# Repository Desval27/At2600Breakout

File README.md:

# Breadboard Friendly Breakout Board for Atari&trade; 2600 Cartridges

## Ready to Order Gerber Files
- [Default](hardware/gerber_to_order/At2600Breakout_22.86x35.56mm_for_Default.zip)
- [Elecrow](hardware/gerber_to_order/At2600Breakout_22.86x35.56mm_for_Elecrow.zip)
- [FusionPCB](hardware/gerber_to_order/At2600Breakout_22.86x35.56mm_for_FusionPCB.zip)
- [JLCPCB](hardware/gerber_to_order/At2600Breakout_22.86x35.56mm_for_JLCPCB.zip)
- [PCBWay](hardware/gerber_to_order/At2600Breakout_22.86x35.56mm_for_PCBWay.zip)

## ⚠️ Disclaimer

This project is provided **"as is"**, without warranty of any kind, express or implied,
including but not limited to the warranties of merchantability, fitness for a
particular purpose, and noninfringement.

This is a DIY electronics project intended for educational and experimental use.
Use at your own risk.

The author assumes **no responsibility or liability** for any damage, injury, or loss
resulting from the use or misuse of this design, including but not limited to:

* Damage to connected equipment (Eurorack modules, power supplies, computers, etc.)
* Incorrect assembly or wiring
* Use with incompatible voltages or signal levels
* Personal injury

### Electrical Safety

This project may interface with:

* ±12V Eurorack power rails
* External control voltages (CV)
* Digital and analog circuitry

Improper handling may result in damage or unsafe conditions.

You are responsible for:

* Verifying all connections before powering the system
* Ensuring correct polarity of power connections
* Confirming voltage ranges and signal compatibility
* Using appropriate protection circuits where necessary

### No Guarantees

Schematics, PCB layouts, and code are provided for reference only.
They may contain errors, omissions, or design flaws.

**Always review and validate the design before building or using it.**

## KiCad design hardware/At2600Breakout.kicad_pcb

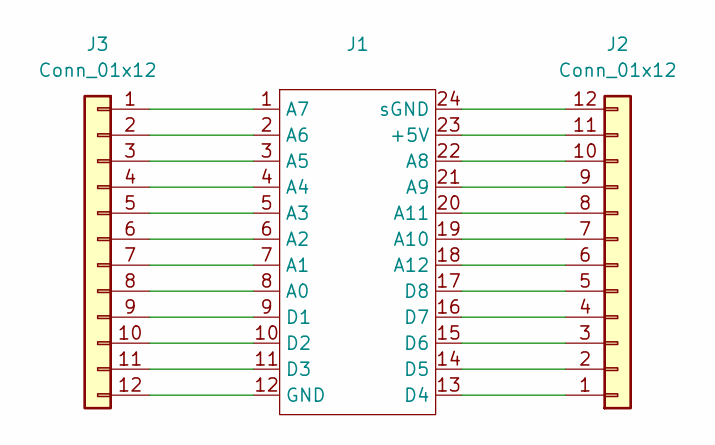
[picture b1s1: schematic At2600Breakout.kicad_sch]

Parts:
J1: 02x12 Cartridge Connector
J2, J3: Conn_01x12; PinHeader_1x12_P2.54mm_Vertical

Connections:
unnamed: J1.23 (+5V), J2.11
unnamed: J1.8 (A0), J3.8
unnamed: J1.7 (A1), J3.7
unnamed: J1.6 (A2), J3.6
unnamed: J1.5 (A3), J3.5
unnamed: J1.4 (A4), J3.4
unnamed: J1.3 (A5), J3.3
unnamed: J1.2 (A6), J3.2
unnamed: J1.1 (A7), J3.1
unnamed: J1.22 (A8), J2.10
unnamed: J1.21 (A9), J2.9
unnamed: J1.19 (A10), J2.7
unnamed: J1.20 (A11), J2.8
unnamed: J1.18 (A12), J2.6
unnamed: J1.9 (D1), J3.9
unnamed: J1.10 (D2), J3.10
unnamed: J1.11 (D3), J3.11
unnamed: J1.13 (D4), J2.1
unnamed: J1.14 (D5), J2.2
unnamed: J1.15 (D6), J2.3
unnamed: J1.16 (D7), J2.4
unnamed: J1.17 (D8), J2.5
unnamed: J1.12 (GND), J3.12
unnamed: J1.24 (sGND), J2.12

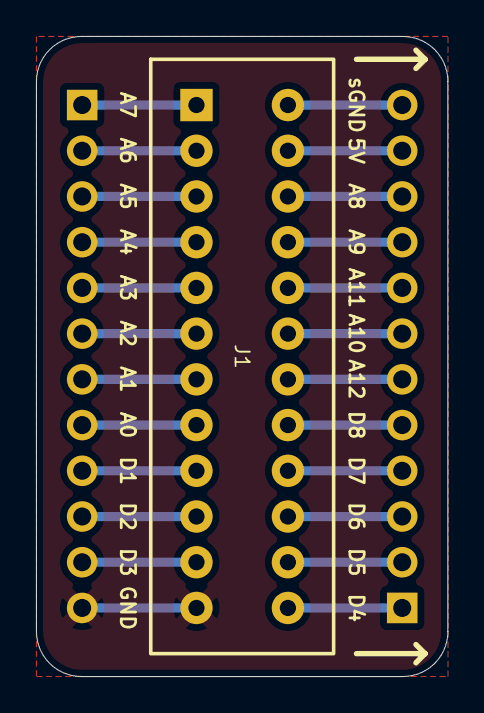
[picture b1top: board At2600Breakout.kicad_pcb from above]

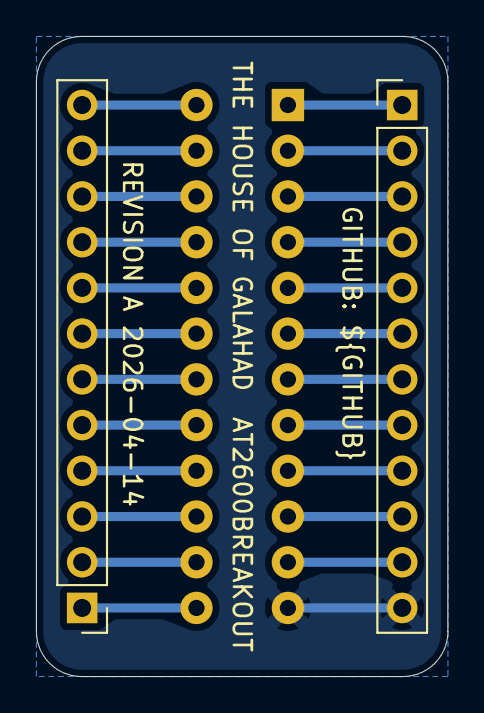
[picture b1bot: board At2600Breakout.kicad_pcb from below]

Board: 2 copper layers, 22.9 x 35.6 mm, 3 parts (2 on the bottom side), 24 nets.

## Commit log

2026-04-14 Add disclaimer and safety information to README
    Added project disclaimer and electrical safety guidelines.
2026-04-14 Add MIT License to the project
2026-04-19 Fix formatting and update title in README.md
2026-04-19 Added Gerber to Order Files
2026-04-19 Fix gitignore
2026-04-19 Fix git
2026-04-19 Add Gerber file links for ordering
    Added links to Gerber files for ordering from various manufacturers.
2026-04-19 Fix formatting of Gerber files section in README
